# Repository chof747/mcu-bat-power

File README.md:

# mcu-bat-power

Battery power board for 5v compatible MCU boards featuring a LiFePo4 Holder

## Idea

This project is a battery supplied power circuitry to supply microcontroller projects with 5V battery power + the ability to charge and protect a LiFePo4 battery. In addition breakout for the USB data lines, voltage and current 
measurement as well as the sensing pins of the charging circuit are added so that a proper power management from
the microcontroller on an attached board is possible.

The concept of the board is to act as an add on board for a microcontroller board in a way that it can work for
several battery powered projects.

The idea is based on a Great Scott's video and materials of a [DIY LiPo Charge/Protect/5V Boost Circuit](https://www.youtube.com/watch?v=Fj0XuYiE7HU&t=618s)

## Components
This board includes a:

- LiFePo4 charging IC (CN3058E)
- Battery protection circuitry (HY2112 + FS8205)
- 5V Boost converter (MT3608 + passive components)
- A Micro USB socket to charge it conviniently from micro USB
- A power measurement circuit (INA219AxD with a 100mOhm sensing resistor)
- Leds for Power, Charging and Done
- A Power Switch
- Three connectors for other boards:
    - 5V/GND
    - Signals and Measuring:
        - Chargin and Done signal from the charging IC
        - I2C Bus for INA219A
        - VREF and GND connections to bring in the voltage level and power from a specific microcontroller
    - D+/D- from the USB Line

## Schematic & Board Layout

## Revision History:

- **v1.0**: Initial version (Produced: 13.03.2024)<br/>
  This initial version includes a view additional features to enable better testing:
    - Test pads for all important voltage levels, signals and gnd
    - Additional pads to pass 5V power from a power supply
    - a bit more space (battery and circiutry are on the same side of the board)

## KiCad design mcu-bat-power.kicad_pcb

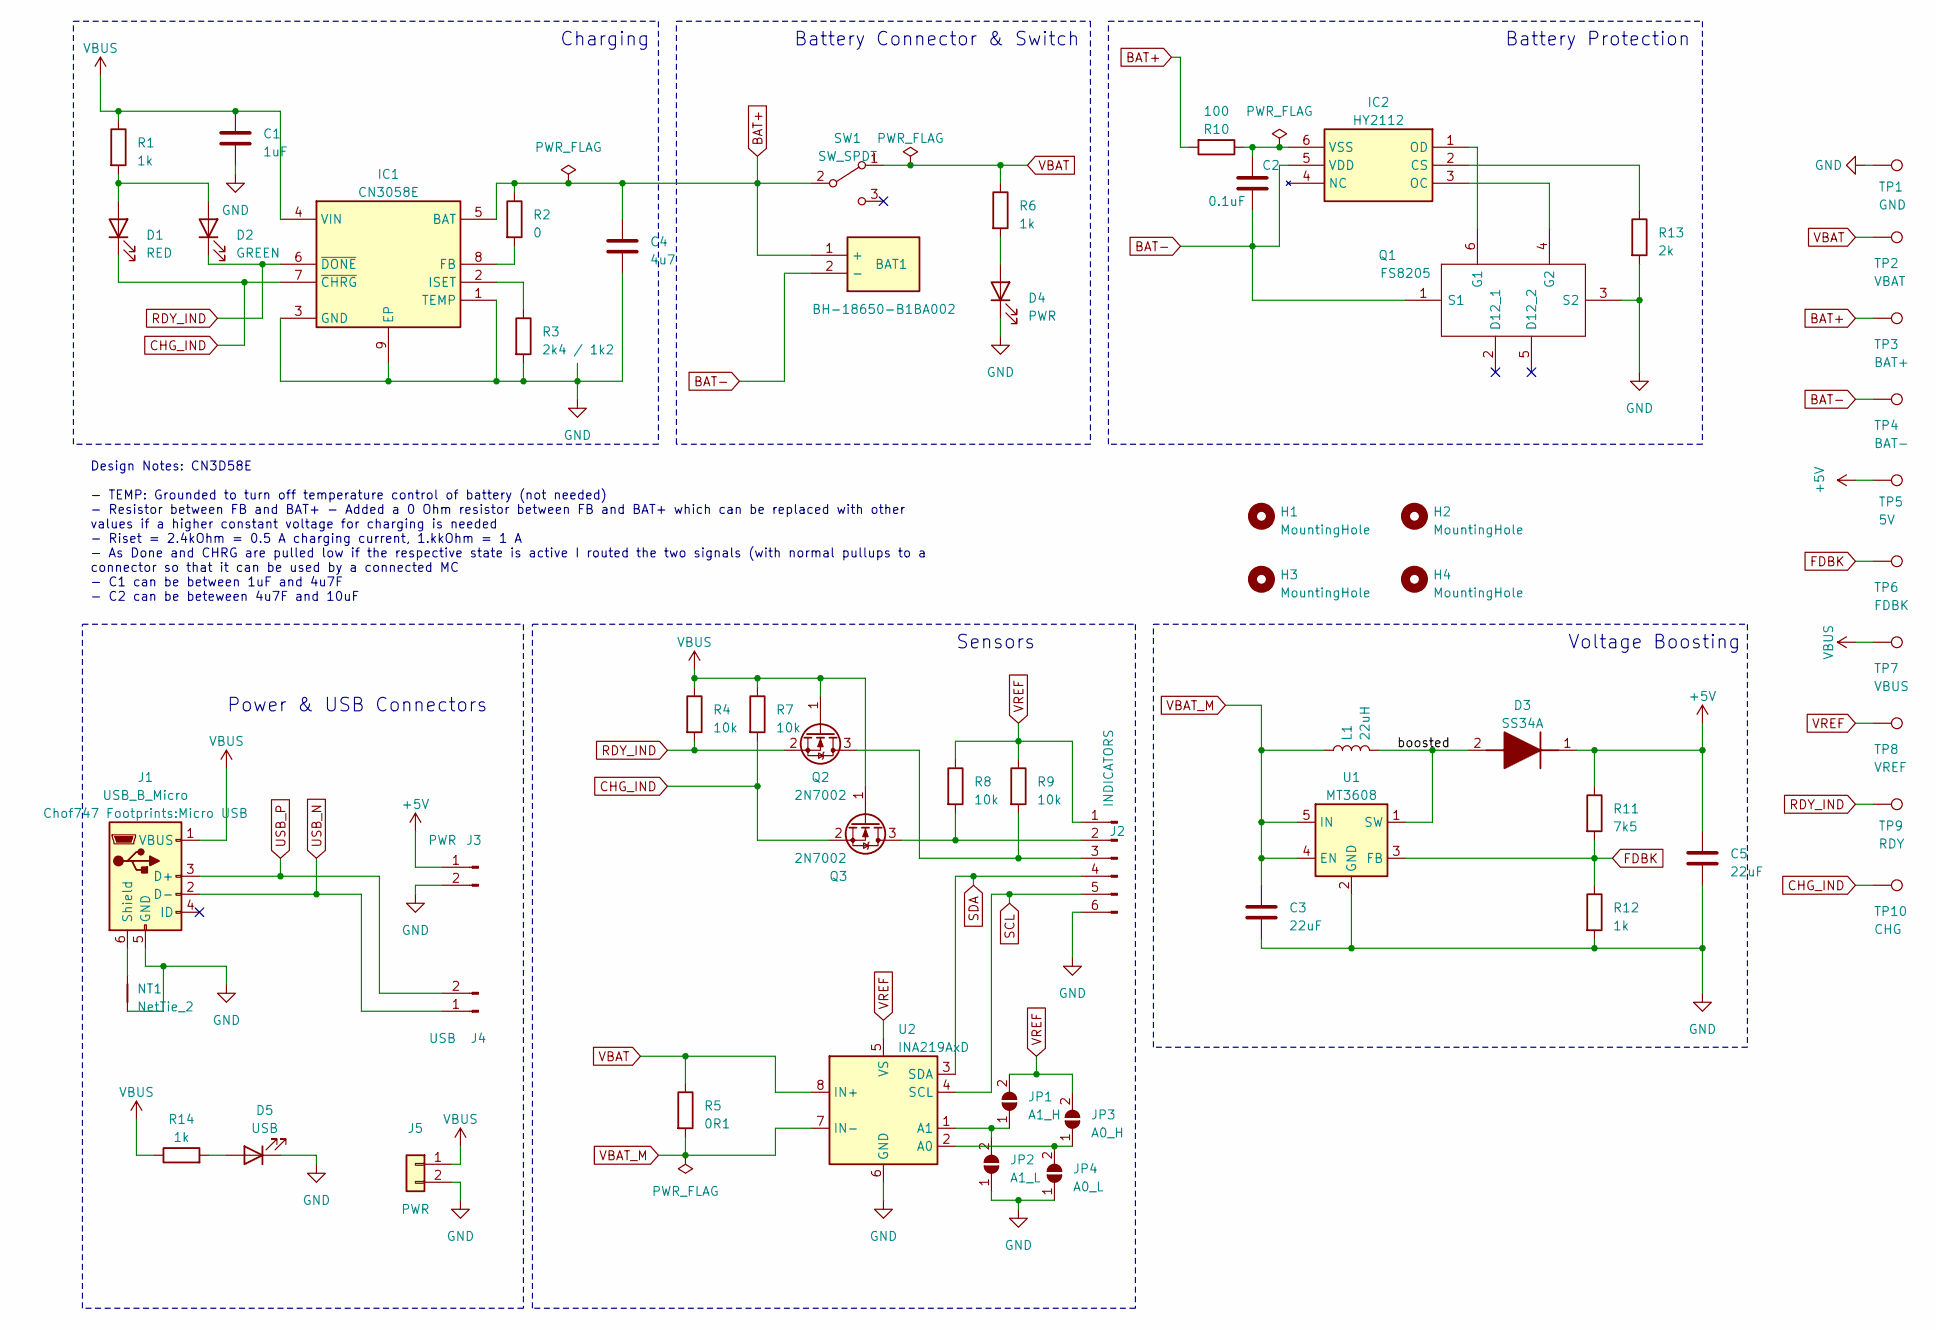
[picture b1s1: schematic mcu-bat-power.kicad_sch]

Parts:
BAT1: BH-18650-B1BA002; BH18650B1BA002; Manufacturer_Part_Number BH-18650-B1BA002
C1: 1uF; C_0603_1608Metric_Pad1.08x0.95mm_HandSolder
C2: 0.1uF; C_0603_1608Metric_Pad1.08x0.95mm_HandSolder
C3, C5: 22uF; C_1206_3216Metric_Pad1.33x1.80mm_HandSolder
C4: 4u7; C_0603_1608Metric_Pad1.08x0.95mm_HandSolder
D1: RED; LED_0603_1608Metric_Pad1.05x0.95mm_HandSolder
D2: GREEN; LED_0603_1608Metric_Pad1.05x0.95mm_HandSolder
D3: SS34A; DIOM5026X262N; Manufacturer_Part_Number SS34A
D4: PWR; LED_0603_1608Metric_Pad1.05x0.95mm_HandSolder
D5: USB; LED_0603_1608Metric_Pad1.05x0.95mm_HandSolder
H1, H2, H3, H4: MountingHole; MountingHole_3.2mm_M3-smallBorder
IC1: CN3058E; SOIC127P600X175-9N; Manufacturer_Part_Number CN3058E
IC2: HY2112; SOT95P280X145-6N; Manufacturer_Part_Number HY2112
J1: USB_B_Micro; Micro USB
J2: INDICATORS; PinHeader_1x06_P2.54mm_Horizontal
J3: PWR; PinHeader_1x02_P2.54mm_Horizontal
J4: USB; PinHeader_1x02_P2.54mm_Horizontal
J5: PWR; pad_1x2_1.5mmx3mm
JP1: A1_H; SolderJumper-2_P1.3mm_Open_RoundedPad1.0x1.5mm
JP2: A1_L; SolderJumper-2_P1.3mm_Open_RoundedPad1.0x1.5mm
JP3: A0_H; SolderJumper-2_P1.3mm_Open_RoundedPad1.0x1.5mm
JP4: A0_L; SolderJumper-2_P1.3mm_Open_RoundedPad1.0x1.5mm
L1: 22uH; SMD0740
NT1: NetTie_2; NetTie-2_SMD_Pad0.5mm
Q1: FS8205; Manufacturer_Part_Number FS8205
Q2, Q3: 2N7002; SOT-23
R1, R6, R12, R14: 1k; R_0603_1608Metric_Pad0.98x0.95mm_HandSolder
R2: 0; R_0603_1608Metric_Pad0.98x0.95mm_HandSolder
R3: 2k4 / 1k2; R_0603_1608Metric_Pad0.98x0.95mm_HandSolder
R4, R7, R8, R9: 10k; R_0603_1608Metric_Pad0.98x0.95mm_HandSolder
R5: 0R1; R_2512_6332Metric_Pad1.40x3.35mm_HandSolder
R10: 100; R_0603_1608Metric_Pad0.98x0.95mm_HandSolder
R11: 7k5; R_0603_1608Metric_Pad0.98x0.95mm_HandSolder
R13: 2k; R_0603_1608Metric_Pad0.98x0.95mm_HandSolder
SW1: SW_SPDT; Slide-switch-SS-12D11L7
TP1: GND; TestPoint_Pad_2.0x2.0mm
TP2: VBAT; TestPoint_Pad_2.0x2.0mm
TP3: BAT+; TestPoint_Pad_2.0x2.0mm
TP4: BAT-; TestPoint_Pad_2.0x2.0mm
TP5: 5V; TestPoint_Pad_2.0x2.0mm
TP6: FDBK; TestPoint_Pad_2.0x2.0mm
TP7: VBUS; TestPoint_Pad_2.0x2.0mm
TP8: VREF; TestPoint_Pad_2.0x2.0mm
TP9: RDY; TestPoint_Pad_2.0x2.0mm
TP10: CHG; TestPoint_Pad_2.0x2.0mm
U1: MT3608; SOT-23-6
U2: INA219AxD; SOIC-8_3.9x4.9mm_P1.27mm

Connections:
+5V: C5.1, D3.1 (K), J3.1, R11.1, TP5.1
/boosted: D3.2 (A), L1.2, U1.1 (SW)
BAT+: BAT1.1 (+), C4.1, IC1.5 (BAT), R2.1, R10.2, SW1.2 (B), TP3.1
BAT-: BAT1.2 (-), C2.2, IC2.5 (VDD), Q1.1 (S1), TP4.1
CHG_IND: D1.1 (K), IC1.7 (~CHRG), Q3.2 (S), R7.2, TP10.1
FDBK: R11.2, R12.1, TP6.1, U1.3 (FB)
GND: C1.2, C3.2, C4.2, C5.2, D4.1 (K), D5.1 (K), IC1.1 (TEMP), IC1.3 (GND), IC1.9 (EP), J1.5 (GND), J2.6, J3.2, J5.2, JP2.1 (A), JP4.1 (A), NT1.1, Q1.3 (S2), R3.2, R12.2, R13.2, TP1.1, U1.2 (GND), U2.6 (GND)
unnamed: D1.2 (A), D2.2 (A), R1.2
unnamed: D4.2 (A), R6.2
unnamed: D5.2 (A), R14.2
unnamed: IC1.8 (FB), R2.2
unnamed: IC1.2 (ISET), R3.1
unnamed: IC2.2 (CS), R13.1
unnamed: IC2.3 (OC), Q1.4 (G2)
unnamed: IC2.1 (OD), Q1.6 (G1)
unnamed: C2.1, IC2.6 (VSS), R10.1
unnamed: J1.6 (Shield), NT1.2
unnamed: J2.2, Q3.3 (D), R8.2
unnamed: J2.3, Q2.3 (D), R9.2
unnamed: JP1.1 (A), JP2.2 (B), U2.1 (A1)
unnamed: JP3.1 (A), JP4.2 (B), U2.2 (A0)
RDY_IND: D2.1 (K), IC1.6 (~DONE), Q2.2 (S), R4.2, TP9.1
SCL: J2.5, U2.4 (SCL)
SDA: J2.4, U2.3 (SDA)
USB_N: J1.2 (D-), J4.1
USB_P: J1.3 (D+), J4.2
VBAT: R5.1, R6.1, SW1.1 (A), TP2.1, U2.8 (IN+)
VBAT_M: C3.1, L1.1, R5.2, U1.4 (EN), U1.5 (IN), U2.7 (IN-)
VBUS: C1.1, IC1.4 (VIN), J1.1 (VBUS), J5.1, Q2.1 (G), Q3.1 (G), R1.1, R4.1, R7.1, R14.1, TP7.1
VREF: J2.1, JP1.2 (B), JP3.2 (B), R8.1, R9.1, TP8.1, U2.5 (VS)

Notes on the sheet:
Design Notes: CN3D58E - TEMP: Grounded to turn off temperature control of battery (not needed) - Resistor between FB and BAT+ - Added a 0 Ohm resistor between FB and BAT+ which can be replaced with other values if a higher constant voltage for charging is needed - Riset = 2.4kOhm = 0.5 A charging c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
Battery Connector & Switch
Charging
Voltage Boosting
Sensors
Power & USB Connectors
Battery Protection

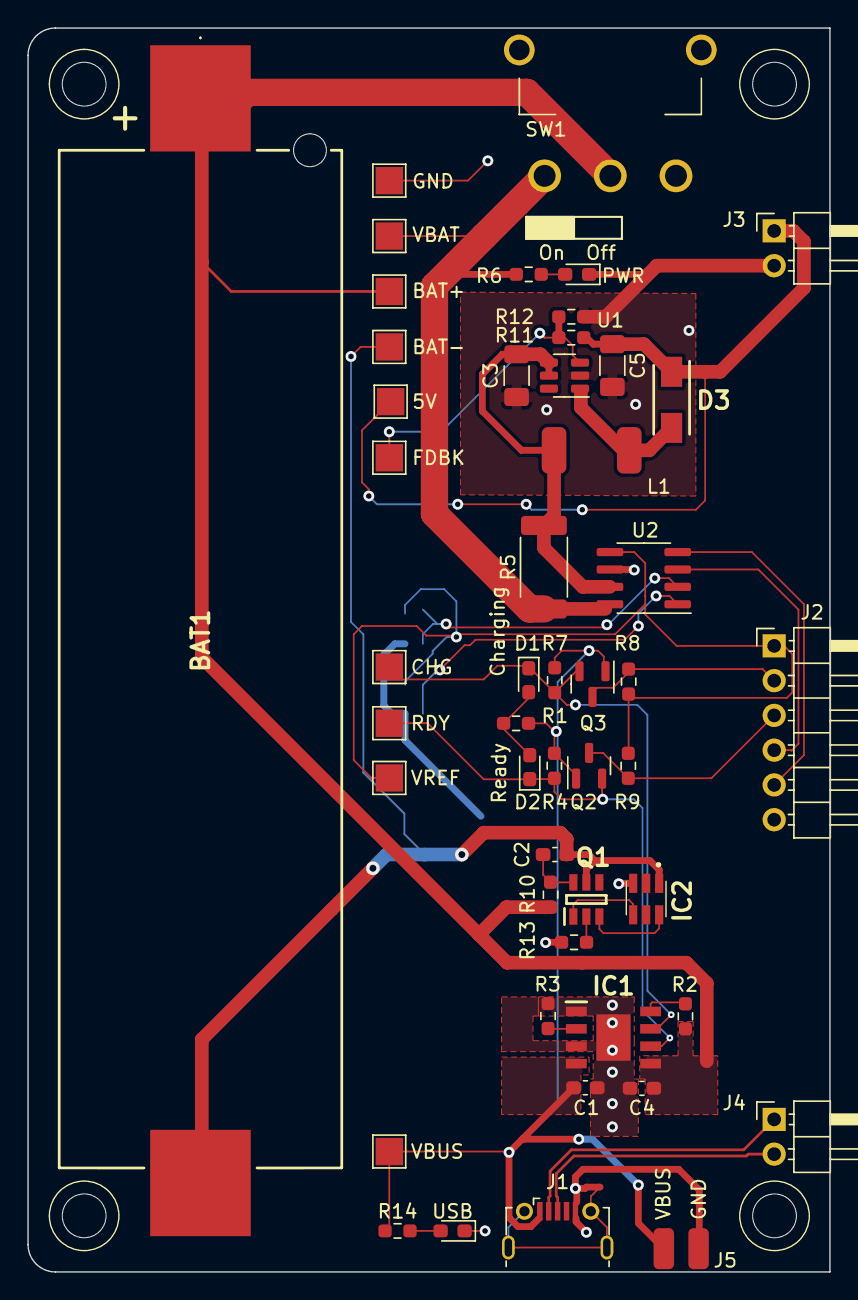
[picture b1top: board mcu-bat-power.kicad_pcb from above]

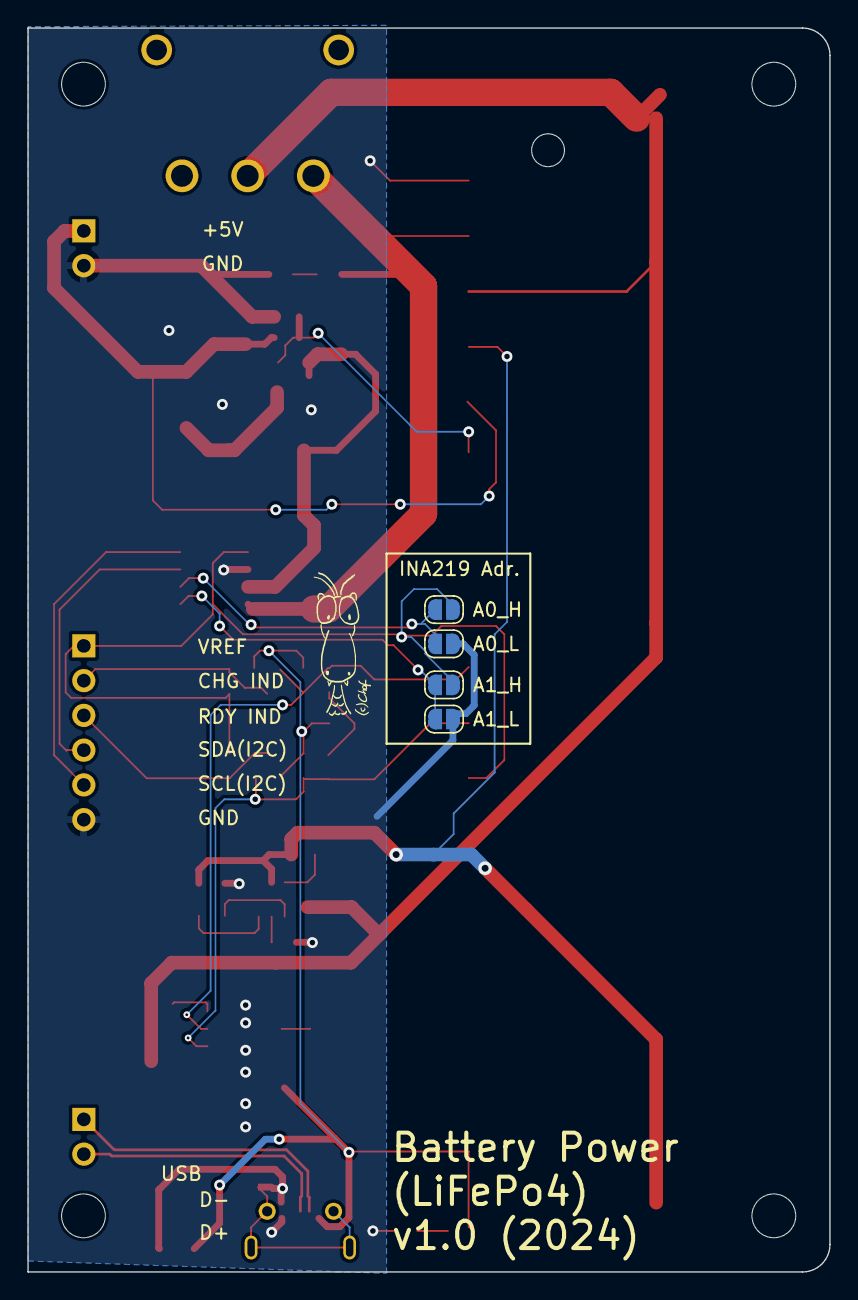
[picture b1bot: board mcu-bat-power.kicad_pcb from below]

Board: 2 copper layers, 58.6 x 90.9 mm, 58 parts (4 on the bottom side), 30 nets.

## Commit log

2023-10-11 renaming and initialization
2023-10-26 First version with all components set and placed
2023-11-05 running dcr checks and excluding unnecessary issues
2024-03-14 Version 1.0 (sent to fabhouse) + updated readme
2024-03-14 upgrade to KiCad 8.0
2024-05-06 Changes due to KiCad8 + setting origin
2024-05-11 Corrected VDD and VSS connection on HY chip
2024-08-29 added kibot from template
2024-08-29 fixed sh issues with kibot
2025-02-14 changes towards new version
